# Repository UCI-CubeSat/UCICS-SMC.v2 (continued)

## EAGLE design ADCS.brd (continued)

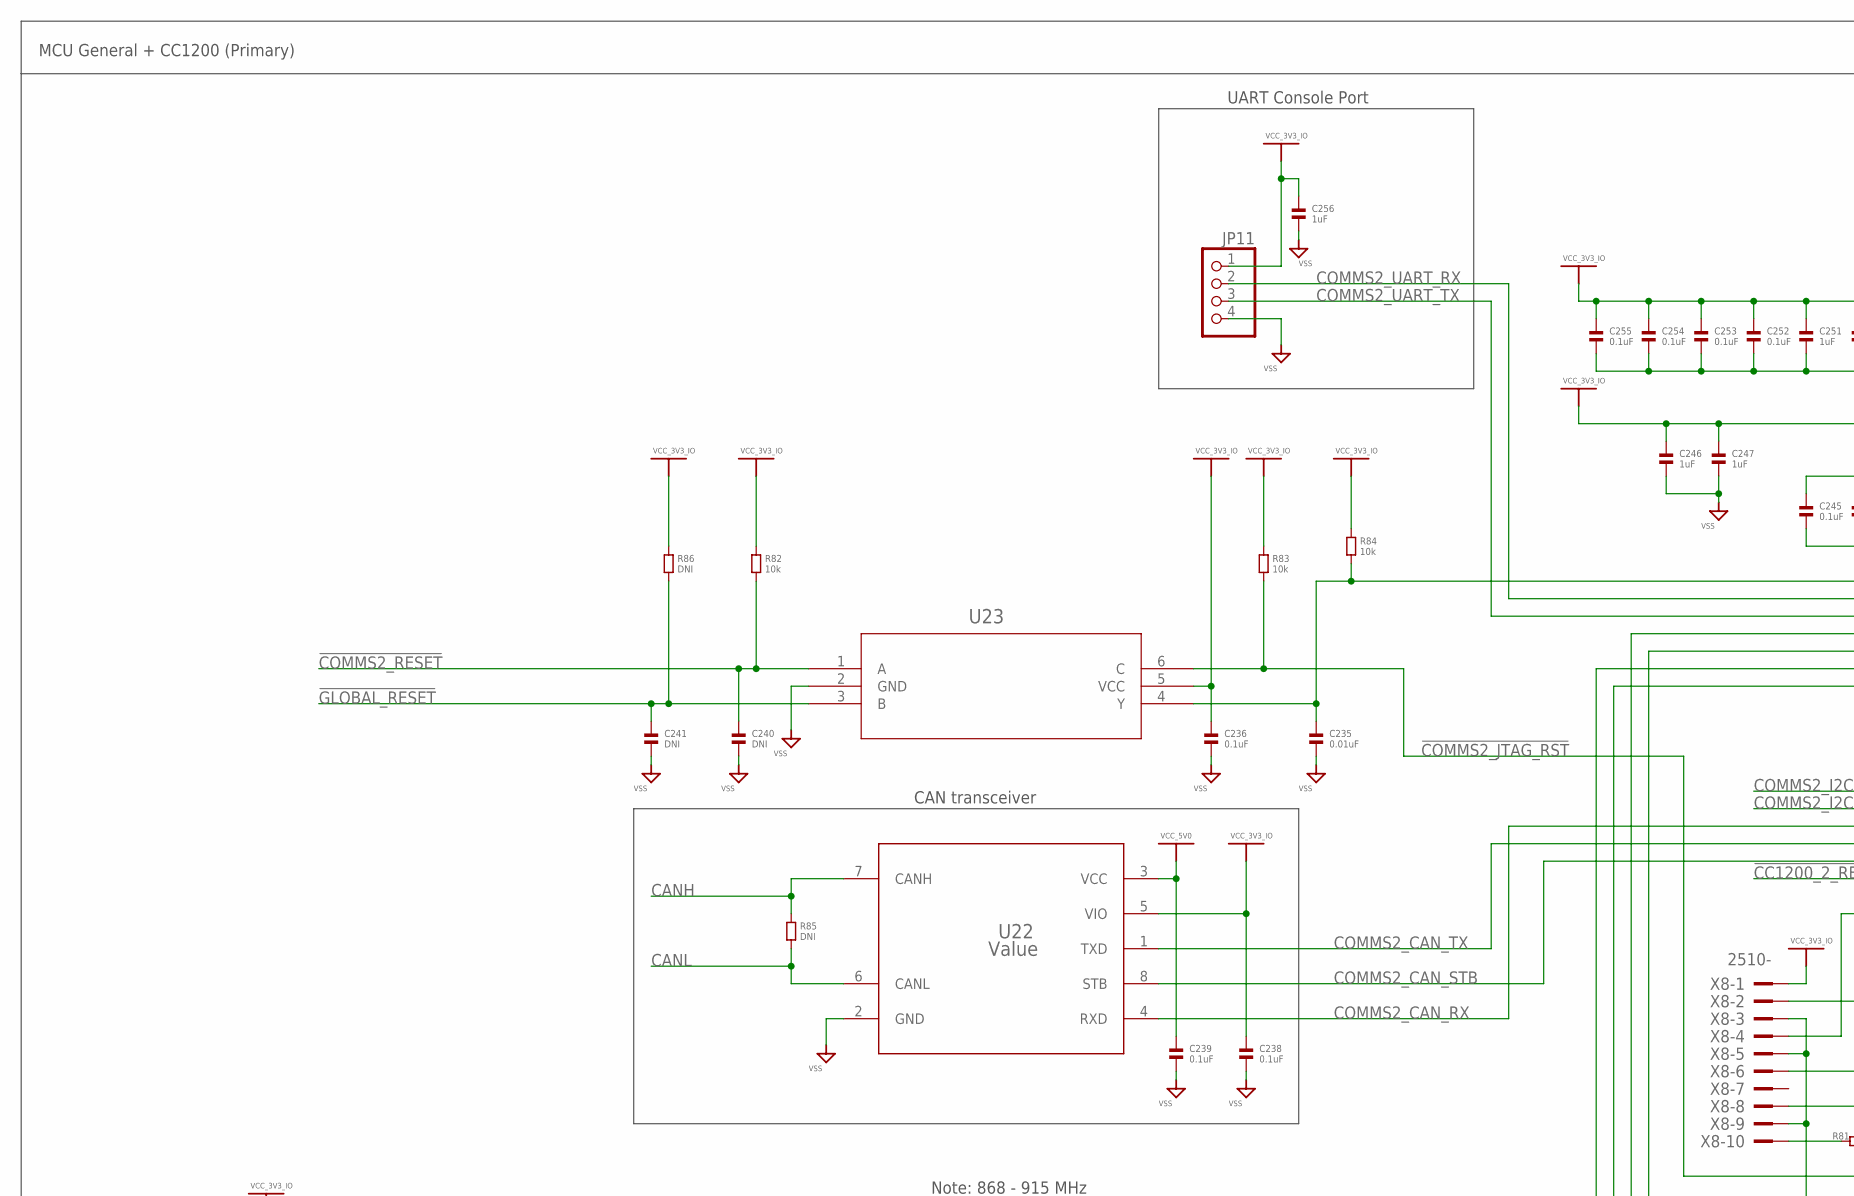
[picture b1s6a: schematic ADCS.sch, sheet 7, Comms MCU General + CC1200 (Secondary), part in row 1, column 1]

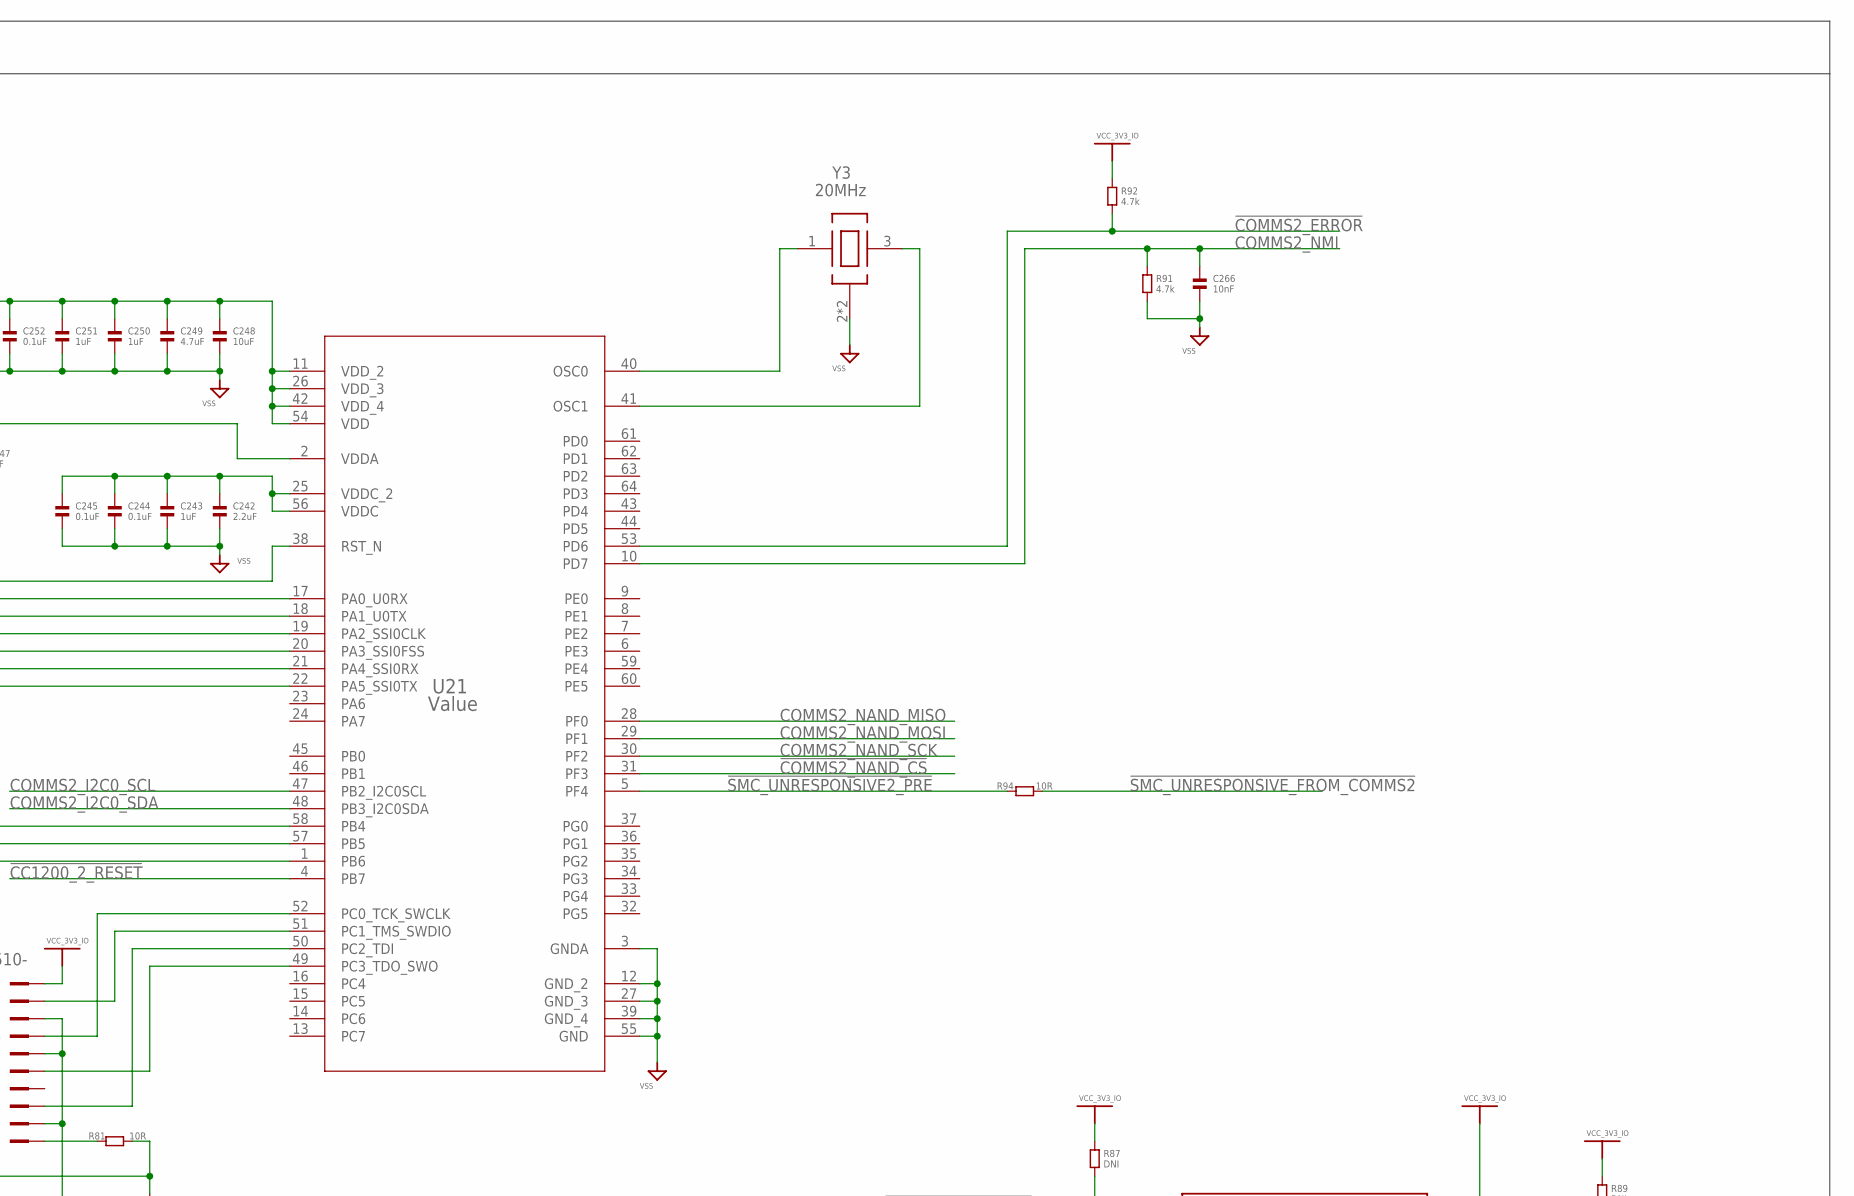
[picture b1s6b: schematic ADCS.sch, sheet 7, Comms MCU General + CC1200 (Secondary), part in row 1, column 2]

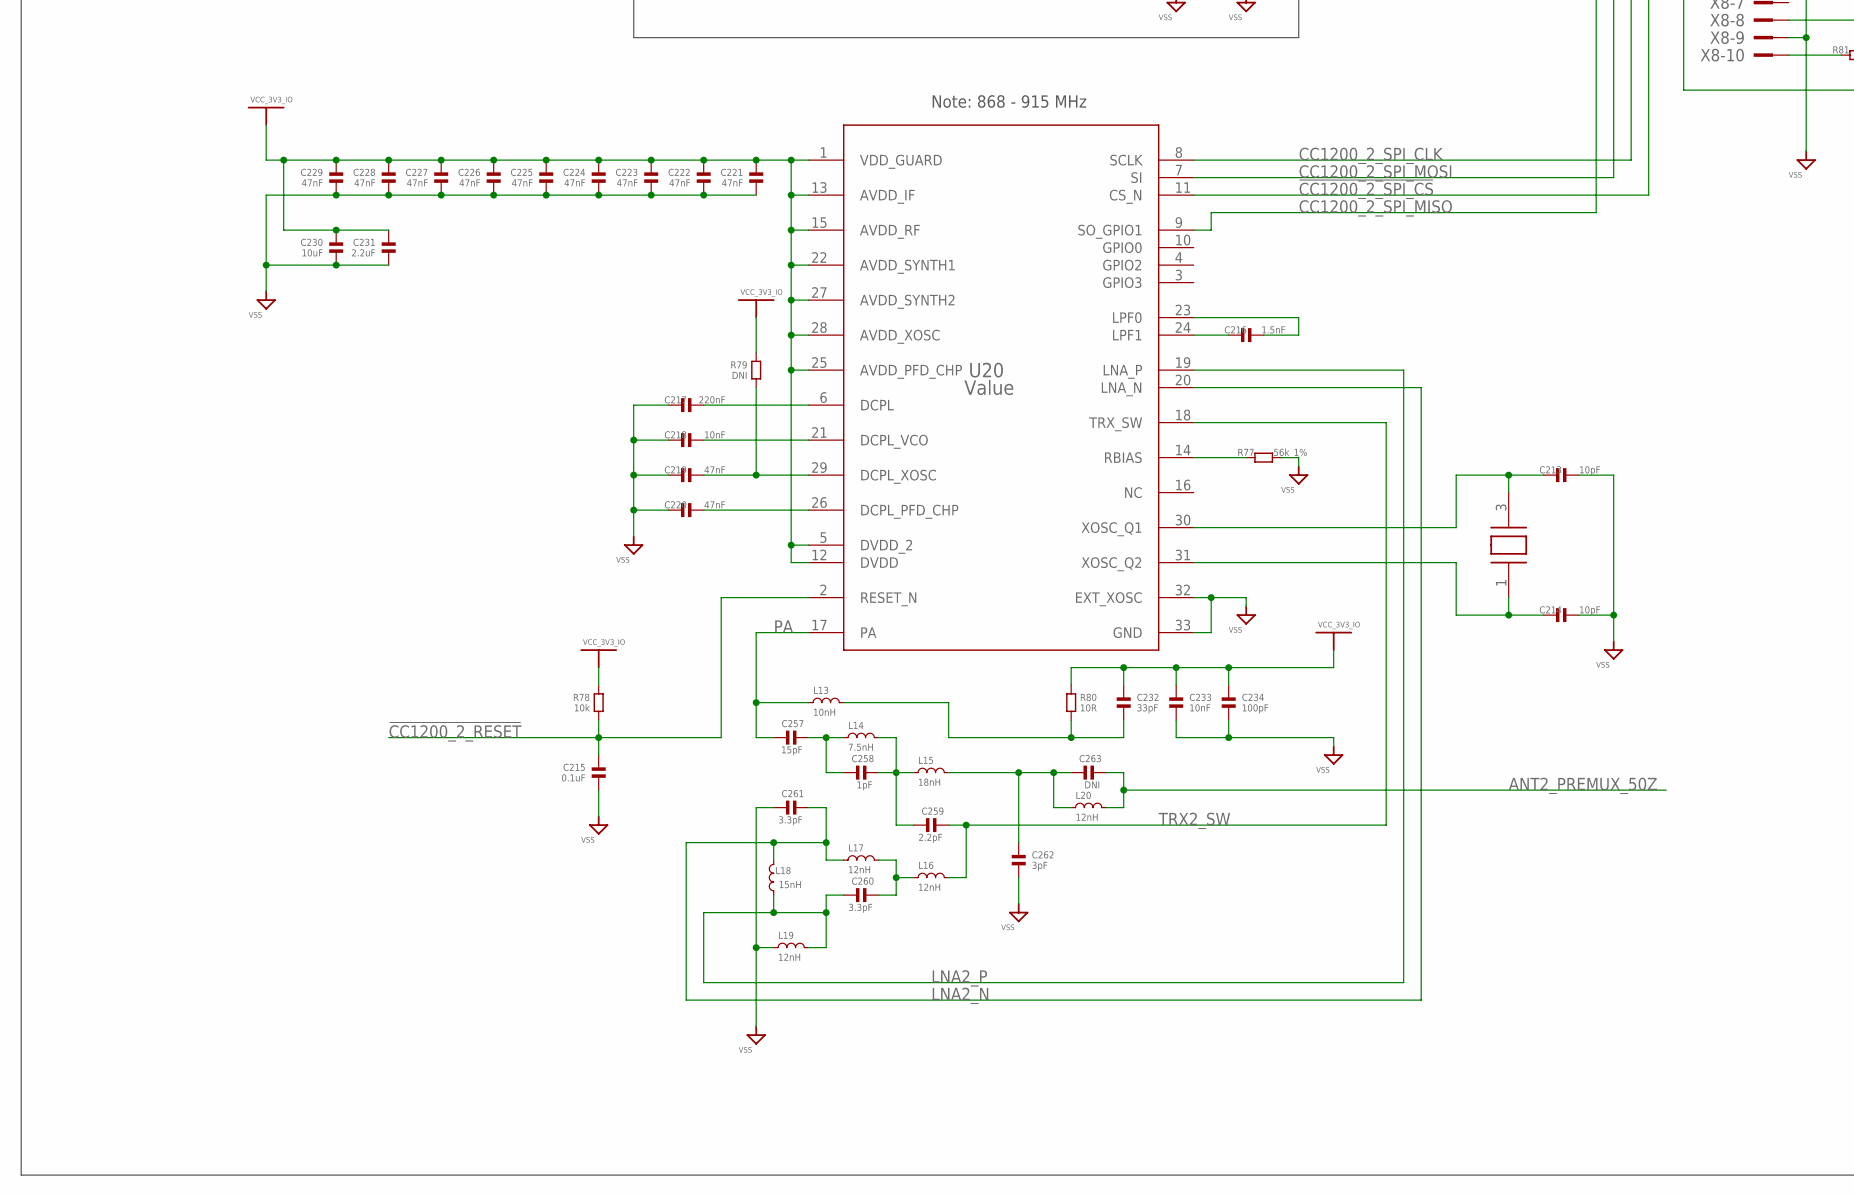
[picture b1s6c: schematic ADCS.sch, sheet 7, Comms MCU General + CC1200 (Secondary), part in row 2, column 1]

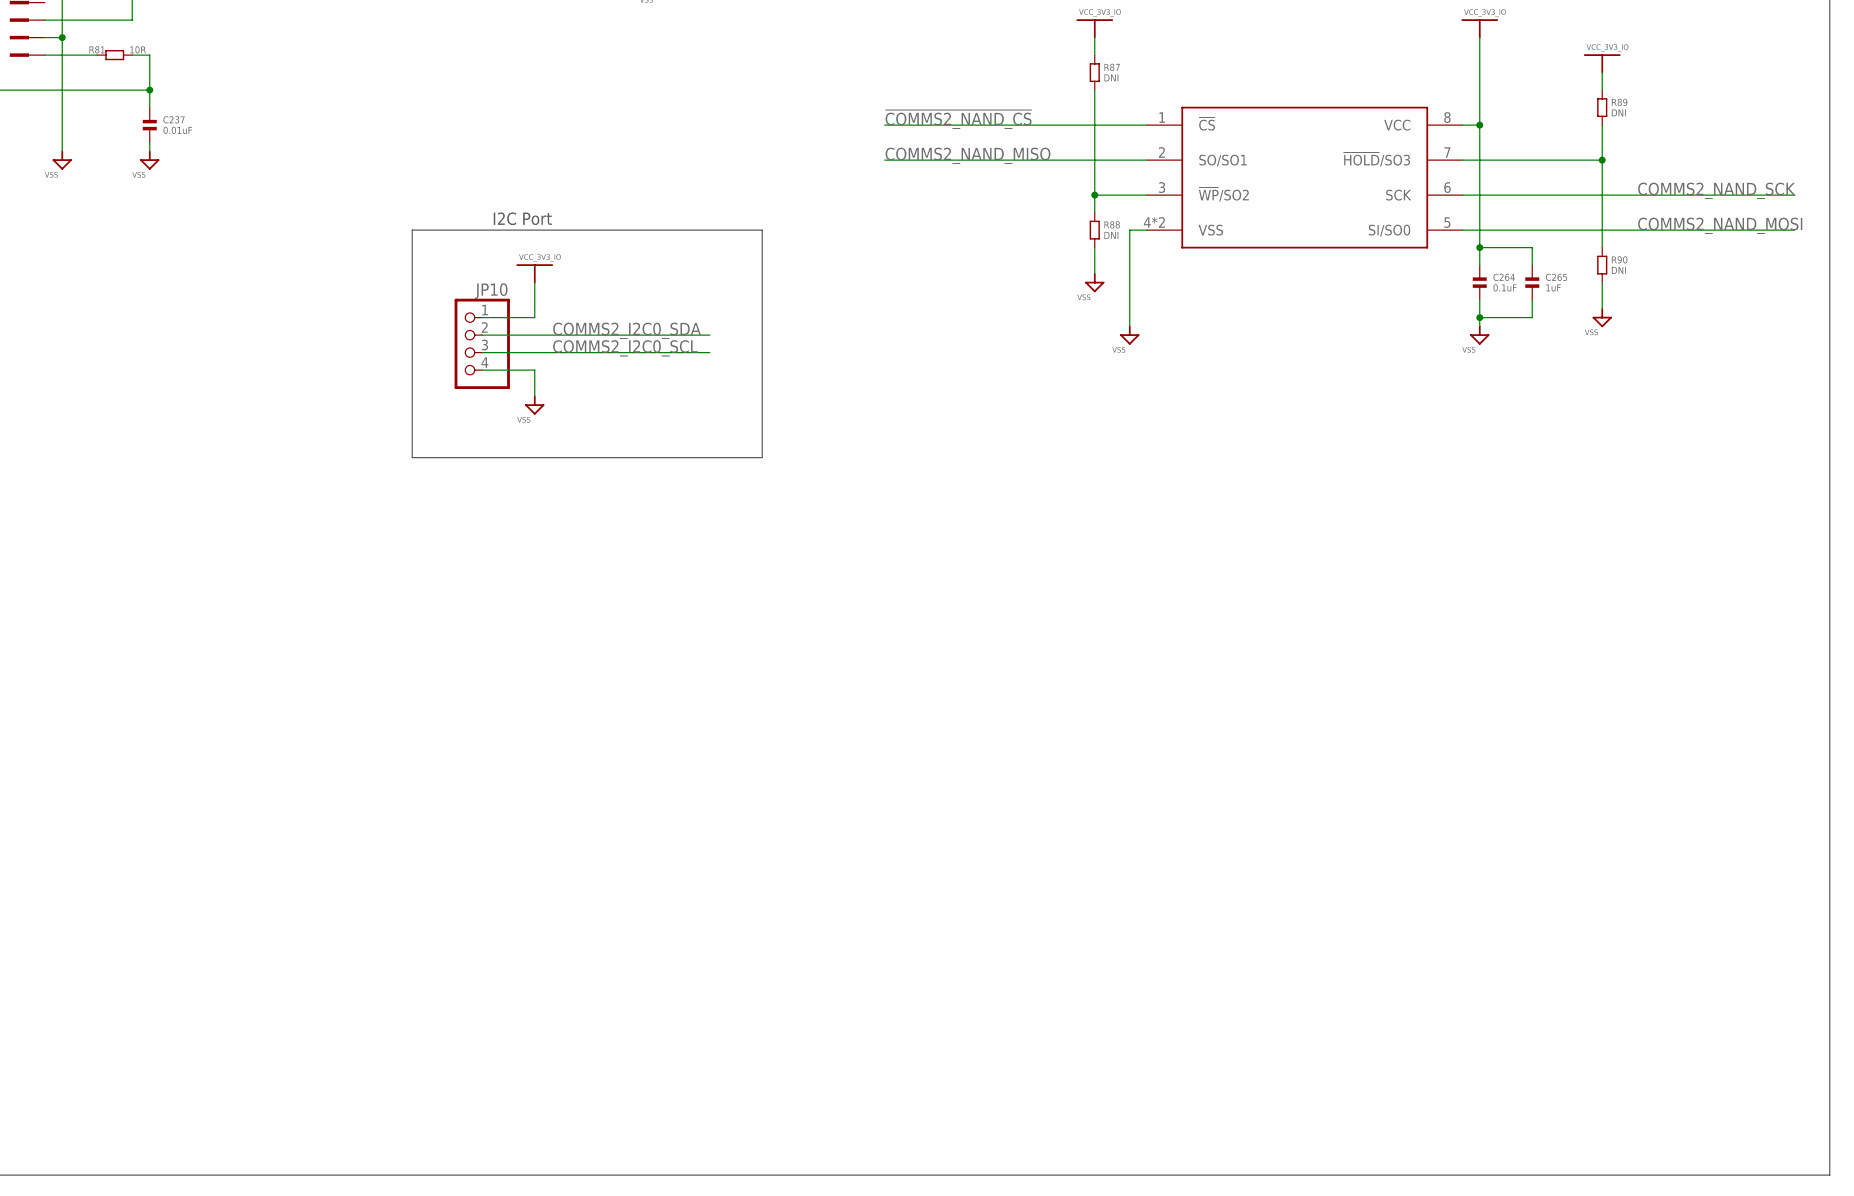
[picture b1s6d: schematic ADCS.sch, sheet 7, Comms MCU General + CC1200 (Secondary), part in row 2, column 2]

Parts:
C213, C214: 10pF; 0603
C215, C236, C238, C239, C244, C245, C252, C253, C254, C255, C264: 0.1uF; 0603
C216: 1.5nF; 0402
C217: 220nF; 0402
C218, C233: 10nF; 0402
C219, C220, C221, C222, C223, C224, C225, C226, C227, C228, C229: 47nF; 0402
C230, C248: 10uF; 0603
C231, C242: 2.2uF; 0603
C232: 33pF; 0402
C234: 100pF; 0402
C235, C237: 0.01uF; 0603
C240, C241: DNI; 0603
C243, C246, C247, C250, C251, C256, C265: 1uF; 0603
C249: 4.7uF; 0603
C257: 15pF; 0402
C258: 1pF; 0402
C259: 2.2pF; 0402
C260, C261: 3.3pF; 0402
C262: 3pF; 0402
C263: DNI; 0402
C266: 10nF; 0603
JP10, JP11: PINHD-1X4; 1X04
L13: 10nH; 0402
L14: 7.5nH; 0402
L15: 18nH; 0402
L16, L17, L19, L20: 12nH; 0402
L18: 15nH; 0402
R77: 56k_1%; 0603
R78, R82, R83, R84: 10k; 0603
R79: DNI; 0402
R80: 10R; 0402
R81, R94: 10R; 0603
R85, R86, R87, R88, R89, R90: DNI; 0603
R91, R92: 4.7k; 0603
U20: Value; TEXAS_INSTRUMENTS-RADAR-CC1200RHBR
U21: Value; PM0064A_N
U22: Value; TEXAS_INSTRUMENTS-CAN_TRANSCEIVER-TCAN1042/LED_DRIVER-TLC59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
U23: TEXAS_INSTRUMENTS-AND_GATE-SN74LVC1G11_DCK_6
U24: KIOXIA_AMERICA-NAND_FLASH-TC58CVG0S3HRAIG
X7: ECS_INC-OSCILLATOR-ECS-400-10-37-CKM-TR
X8: 2510-; PAK100/2500-10
Y3: 20MHz; ESC-OSCILLATOR-ECS_200_9_33B_CTP_TR

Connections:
!CC1200_2_RESET: C215.1, R78.2, U20.2 (RESET_N), U21.4 (PB7)
!CC1200_2_SPI_CS: U20.11 (CS_N), U21.20 (PA3_SSI0FSS)
!COMMS2_ERROR: R92.2, U21.53 (PD6); also elsewhere on the board
!COMMS2_JTAG_RST: C237.1, R81.2, R83.2, U23.6 (C)
!COMMS2_NAND_CS: U21.31 (PF3), U24.1 (!CS)
!COMMS2_RESET: C240.1, R82.2, U23.1 (A); also elsewhere on the board
!GLOBAL_RESET: C241.1, R86.2, U23.3 (B); also elsewhere on the board
!SMC_UNRESPONSIVE2_PRE: R94.1, U21.5 (PF4)
!SMC_UNRESPONSIVE_FROM_COMMS2: R94.2; also elsewhere on the board
ANT2_PREMUX_50Z: C263.2, L20.2; also elsewhere on the board
CANH: R85.1, U22.7 (CANH); also elsewhere on the board
CANL: R85.2, U22.6 (CANL); also elsewhere on the board
CC1200_2_SPI_CLK: U20.8 (SCLK), U21.19 (PA2_SSI0CLK)
CC1200_2_SPI_MISO: U20.9 (SO_GPIO1), U21.21 (PA4_SSI0RX)
CC1200_2_SPI_MOSI: U20.7 (SI), U21.22 (PA5_SSI0TX)
COMMS2_CAN_RX: U21.58 (PB4), U22.4 (RXD)
COMMS2_CAN_STB: U21.1 (PB6), U22.8 (STB)
COMMS2_CAN_TX: U21.57 (PB5), U22.1 (TXD)
COMMS2_I2C0_SCL: JP10.3, U21.47 (PB2_I2C0SCL)
COMMS2_I2C0_SDA: JP10.2, U21.48 (PB3_I2C0SDA)
COMMS2_NAND_MISO: U21.28 (PF0), U24.2 (SO/SO1)
COMMS2_NAND_MOSI: U21.29 (PF1), U24.5 (SI/SO0)
COMMS2_NAND_SCK: U21.30 (PF2), U24.6 (SCK)
COMMS2_NMI: C266.1, R91.1, U21.10 (PD7); also elsewhere on the board
COMMS2_UART_RX: JP11.2, U21.17 (PA0_U0RX); also elsewhere on the board
COMMS2_UART_TX: JP11.3, U21.18 (PA1_U0TX); also elsewhere on the board
LNA2_N: C261.2, L17.1, L18.2, U20.20 (LNA_N)
LNA2_P: C260.1, L18.1, L19.2, U20.19 (LNA_P)
unnamed: R77.1, U20.14 (RBIAS)
unnamed: C213.1, U20.30 (XOSC_Q1), X7.3 (XO)
unnamed: C214.1, U20.31 (XOSC_Q2), X7.1 (XI)
unnamed: C216.1, U20.24 (LPF1)
unnamed: C216.2, U20.23 (LPF0)
unnamed: C220.2, U20.26 (DCPL_PFD_CHP)
unnamed: C219.2, R79.2, U20.29 (DCPL_XOSC)
unnamed: C218.2, U20.21 (DCPL_VCO)
unnamed: C217.2, U20.6 (DCPL)
unnamed: C232.2, L13.2, R80.2
unnamed: R81.1, X8.10
unnamed: C235.1, R84.2, U21.38 (RST_N), U23.4 (Y)
unnamed: U21.50 (PC2_TDI), X8.8
unnamed: U21.49 (PC3_TDO_SWO), X8.6
unnamed: U21.51 (PC1_TMS_SWDIO), X8.2
unnamed: U21.52 (PC0_TCK_SWCLK), X8.4
unnamed: C242.1, C243.1, C244.1, C245.1, U21.25 (VDDC_2), U21.56 (VDDC)
unnamed: U21.40 (OSC0), Y3.1 (XI)
unnamed: U21.41 (OSC1), Y3.3 (XO)
unnamed: C257.2, C258.1, L14.1
unnamed: C258.2, C259.1, L14.2, L15.1
unnamed: C260.2, L16.1, L17.2
unnamed: C262.1, C263.1, L15.2, L20.1
unnamed: R87.2, R88.1, U24.3 (!WP!/SO2)
unnamed: R89.2, R90.1, U24.7 (!HOLD!/SO3)
PA: C257.1, L13.1, U20.17 (PA); also elsewhere on the board
TRX2_SW: C259.2, L16.2, U20.18 (TRX_SW)
VCC_3V3_IO: C221.1, C222.1, C223.1, C224.1, C225.1, C226.1, C227.1, C228.1, C229.1, C230.1, C231.1, C232.1, C233.1, C234.1, C236.1, C238.1, C246.1, C247.1, C248.1, C249.1, C250.1, C251.1, C252.1, C253.1, C254.1, C255.1, C256.1, C264.1, C265.1, JP10.1, JP11.1, R78.1, R79.1, R80.1, R82.1, R83.1, R84.1, R86.1, R87.1, R89.1, R92.1, U20.1 (VDD_GUARD), U20.5 (DVDD_2), U20.12 (DVDD), U20.13 (AVDD_IF), U20.15 (AVDD_RF), U20.22 (AVDD_SYNTH1), U20.25 (AVDD_PFD_CHP), U20.27 (AVDD_SYNTH2), U20.28 (AVDD_XOSC), U21.2 (VDDA), U21.11 (VDD_2), U21.26 (VDD_3), U21.42 (VDD_4), U21.54 (VDD), U22.5 (VIO), U23.5 (VCC), U24.8 (VCC), X8.1; also elsewhere on the board
VCC_5V0: C239.1, U22.3 (VCC); also elsewhere on the board
VSS: C213.2, C214.2, C215.2, C217.1, C218.1, C219.1, C220.1, C221.2, C222.2, C223.2, C224.2, C225.2, C226.2, C227.2, C228.2, C229.2, C230.2, C231.2, C233.2, C234.2, C235.2, C236.2, C237.2, C238.2, C239.2, C240.2, C241.2, C242.2, C243.2, C244.2, C245.2, C246.2, C247.2, C248.2, C249.2, C250.2, C251.2, C252.2, C253.2, C254.2, C255.2, C256.2, C261.1, C262.2, C264.2, C265.2, C266.2, JP10.4, JP11.4, L19.1, R77.2, R88.2, R90.2, R91.2, U20.32 (EXT_XOSC), U20.33 (GND), U21.3 (GNDA), U21.12 (GND_2), U21.27 (GND_3), U21.39 (GND_4), U21.55 (GND), U22.2 (GND), U23.2 (GND), U24.4 (VSS), U24.9 (VSS), X8.3, X8.5, X8.9, Y3.2 (VSS), Y3.4 (VSS); also elsewhere on the board

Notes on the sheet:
Note: 868 - 915 MHz
MCU General + CC1200 (Primary)
CAN transceiver
I2C Port
UART Console Port

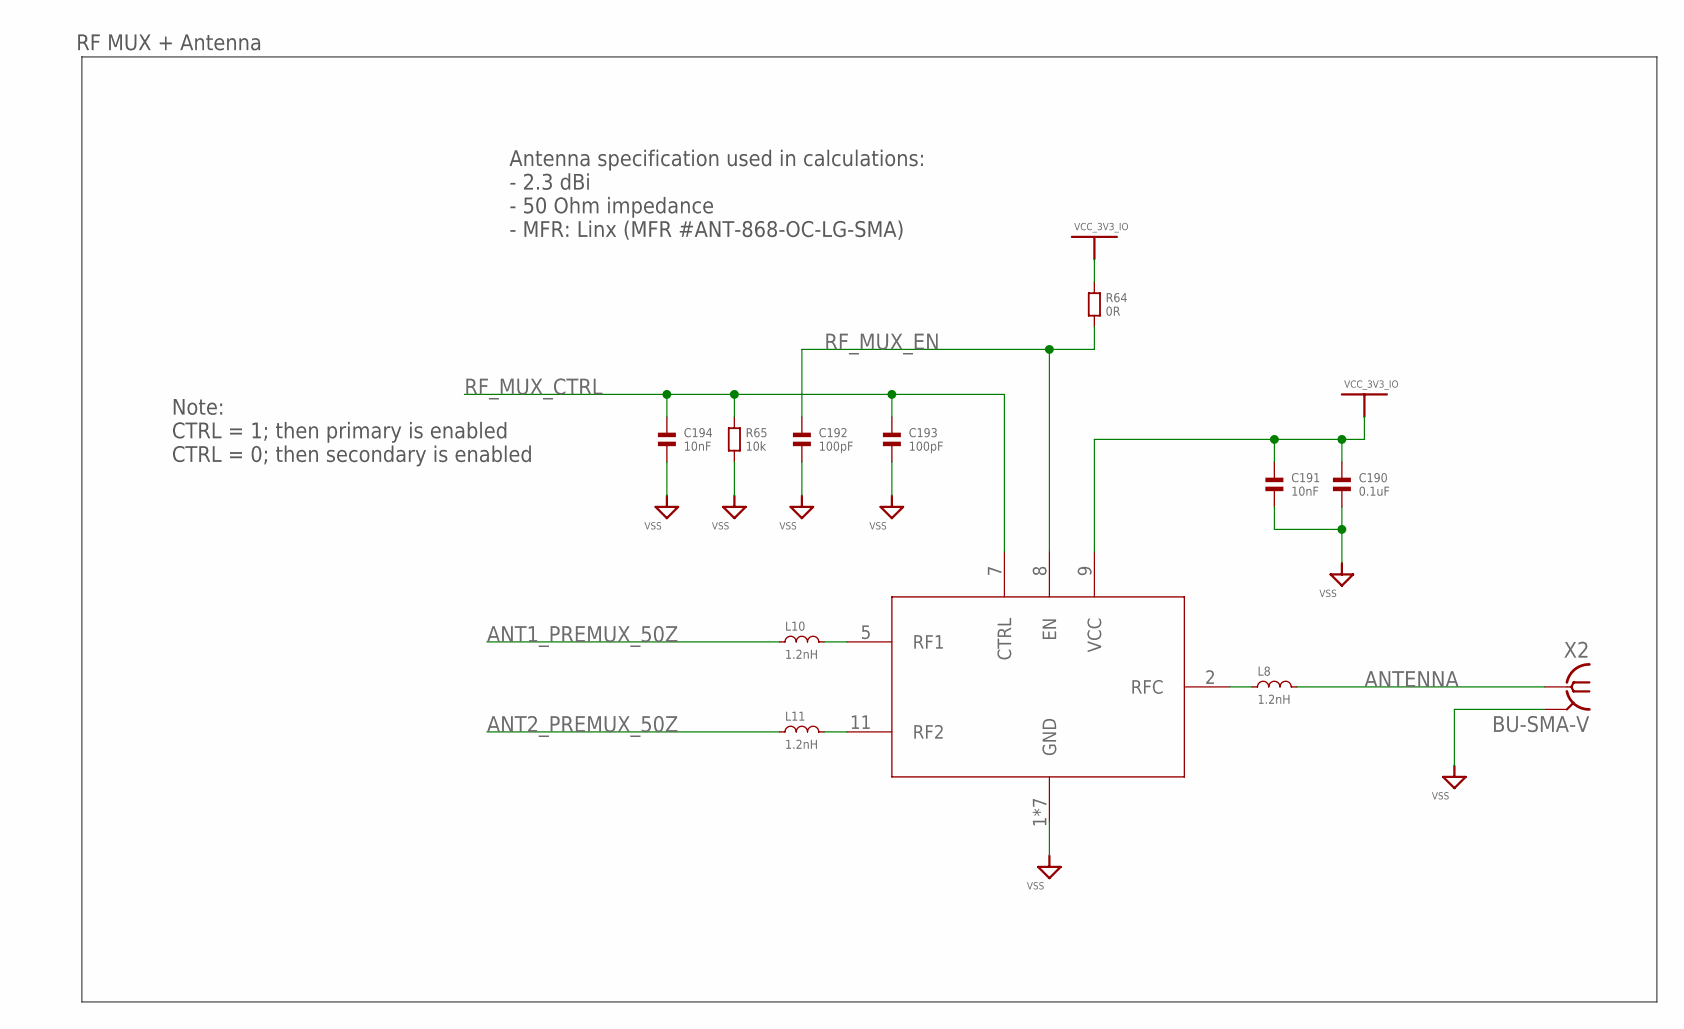
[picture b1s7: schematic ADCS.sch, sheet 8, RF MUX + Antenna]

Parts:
C190: 0.1uF; 0603
C191, C194: 10nF; 0603
C192, C193: 100pF; 0603
L8, L10, L11: 1.2nH; 0402
R64: 0R; 0603
R65: 10k; 0603
U17: QORVO-RF_SWITCH-QPC7512
X2: BU-SMA-V

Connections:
ANT1_PREMUX_50Z: L10.1; also elsewhere on the board
ANT2_PREMUX_50Z: L11.1; also elsewhere on the board
ANTENNA: L8.2, X2.1
unnamed: L8.1, U17.2 (RFC)
unnamed: L11.2, U17.11 (RF2)
unnamed: L10.2, U17.5 (RF1)
RF_MUX_CTRL: C193.1, C194.1, R65.1, U17.7 (CTRL); also elsewhere on the board
RF_MUX_EN: C192.1, R64.2, U17.8 (EN)
VCC_3V3_IO: C190.1, C191.1, R64.1, U17.9 (VCC); also elsewhere on the board
VSS: C190.2, C191.2, C192.2, C193.2, C194.2, R65.2, U17.1 (GND), U17.3 (GND), U17.4 (GND), U17.6 (GND), U17.10 (GND), U17.12 (GND), U17.13 (GND), X2.2, X2.3 (2), X2.4 (2), X2.5 (2); also elsewhere on the board

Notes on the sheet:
Antenna specification used in calculations: - 2.3 dBi - 50 Ohm impedance - MFR: Linx (MFR #ANT-868-OC-LG-SMA)
Note: CTRL = 1; then primary is enabled CTRL = 0; then secondary is enabled
RF MUX + Antenna

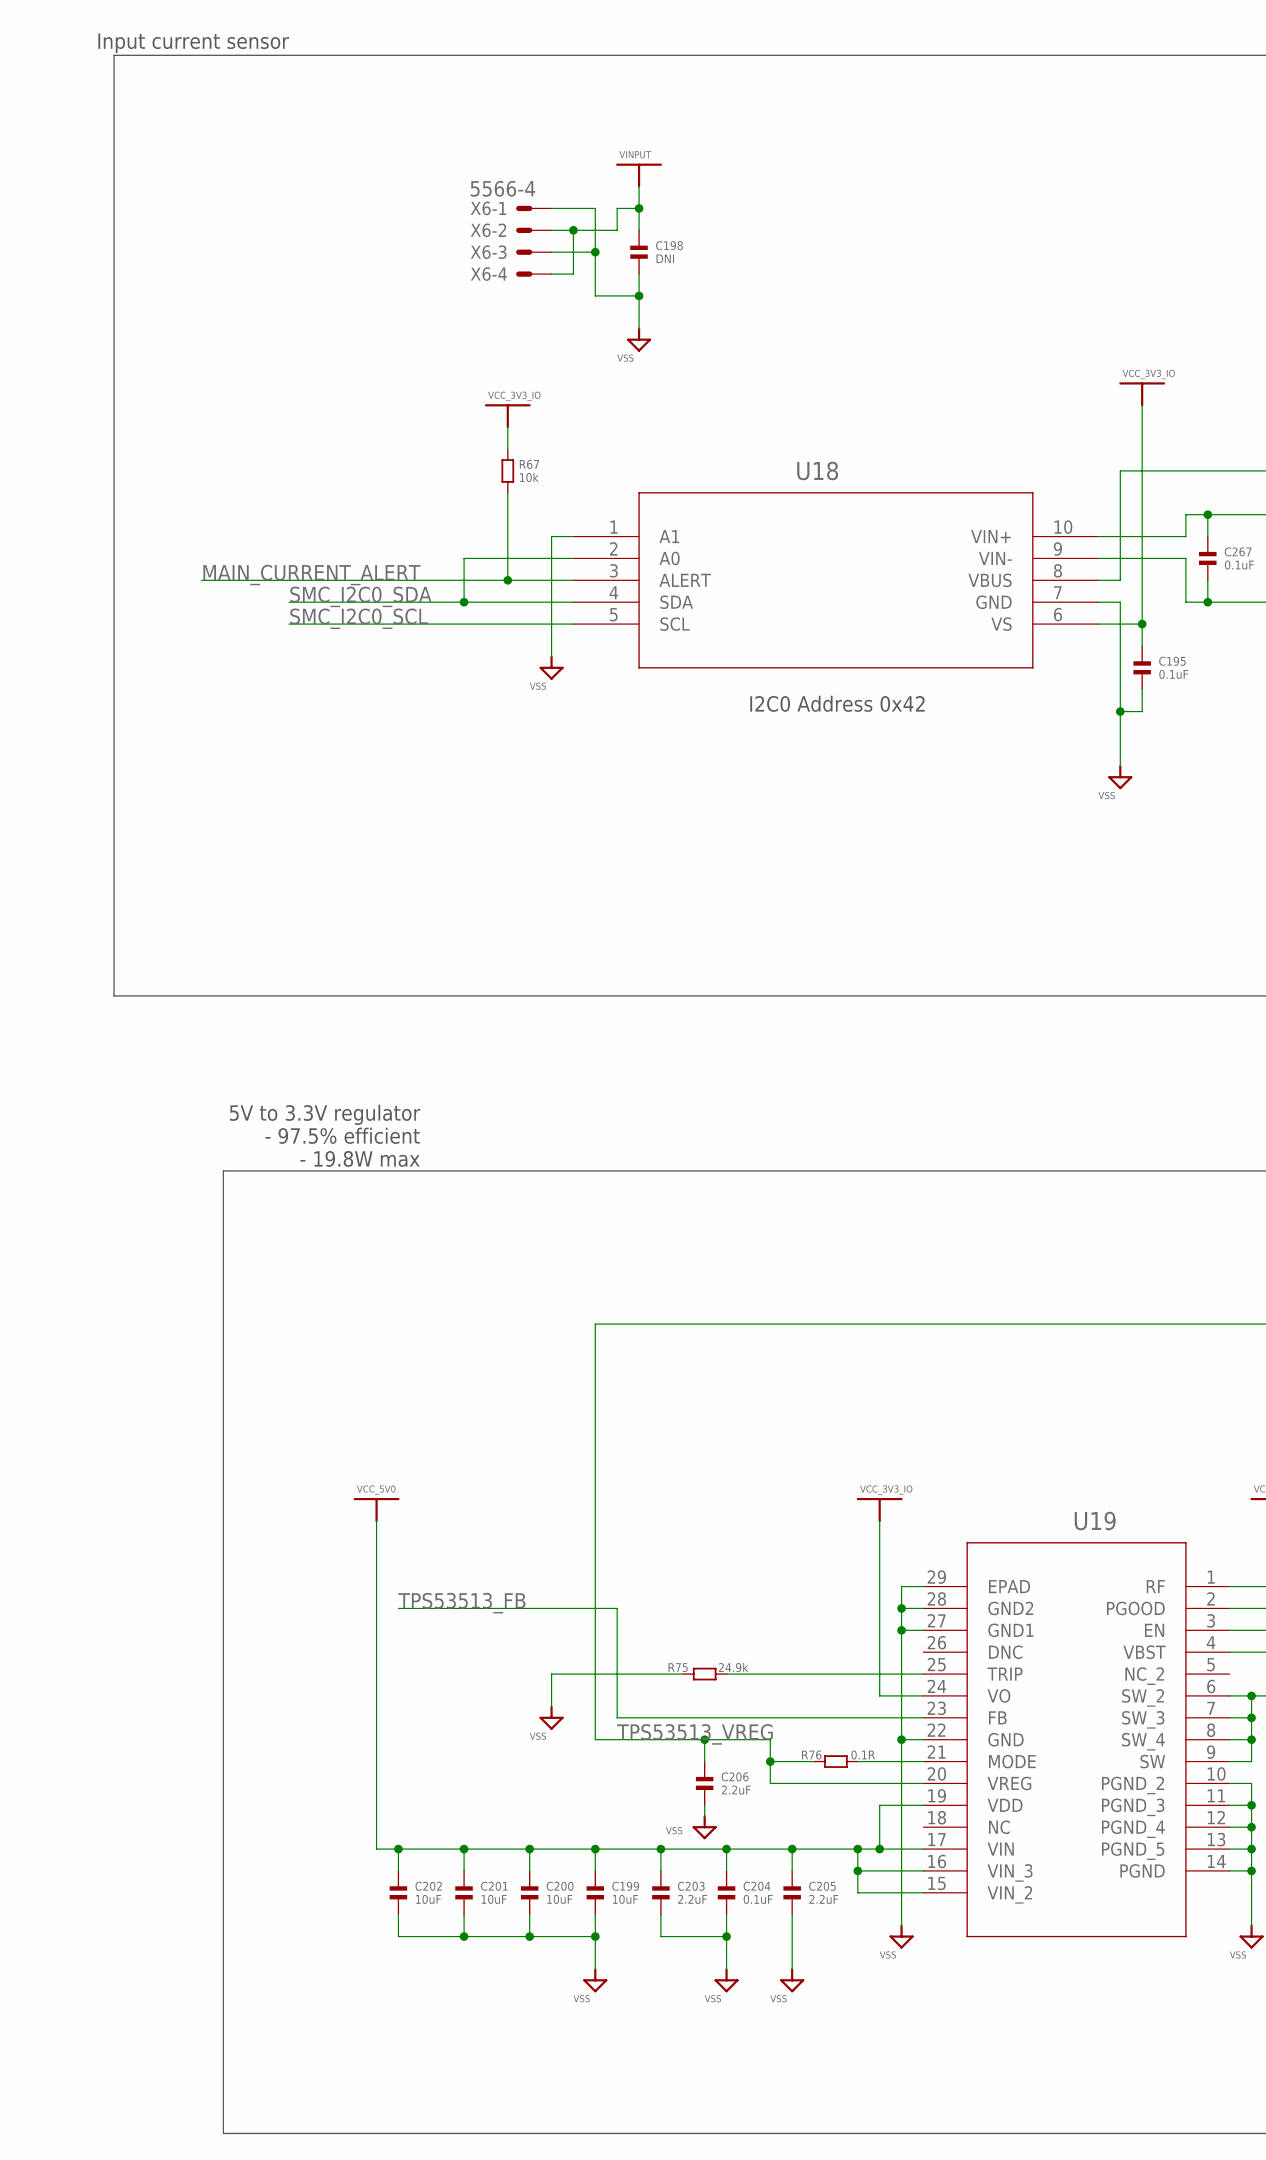
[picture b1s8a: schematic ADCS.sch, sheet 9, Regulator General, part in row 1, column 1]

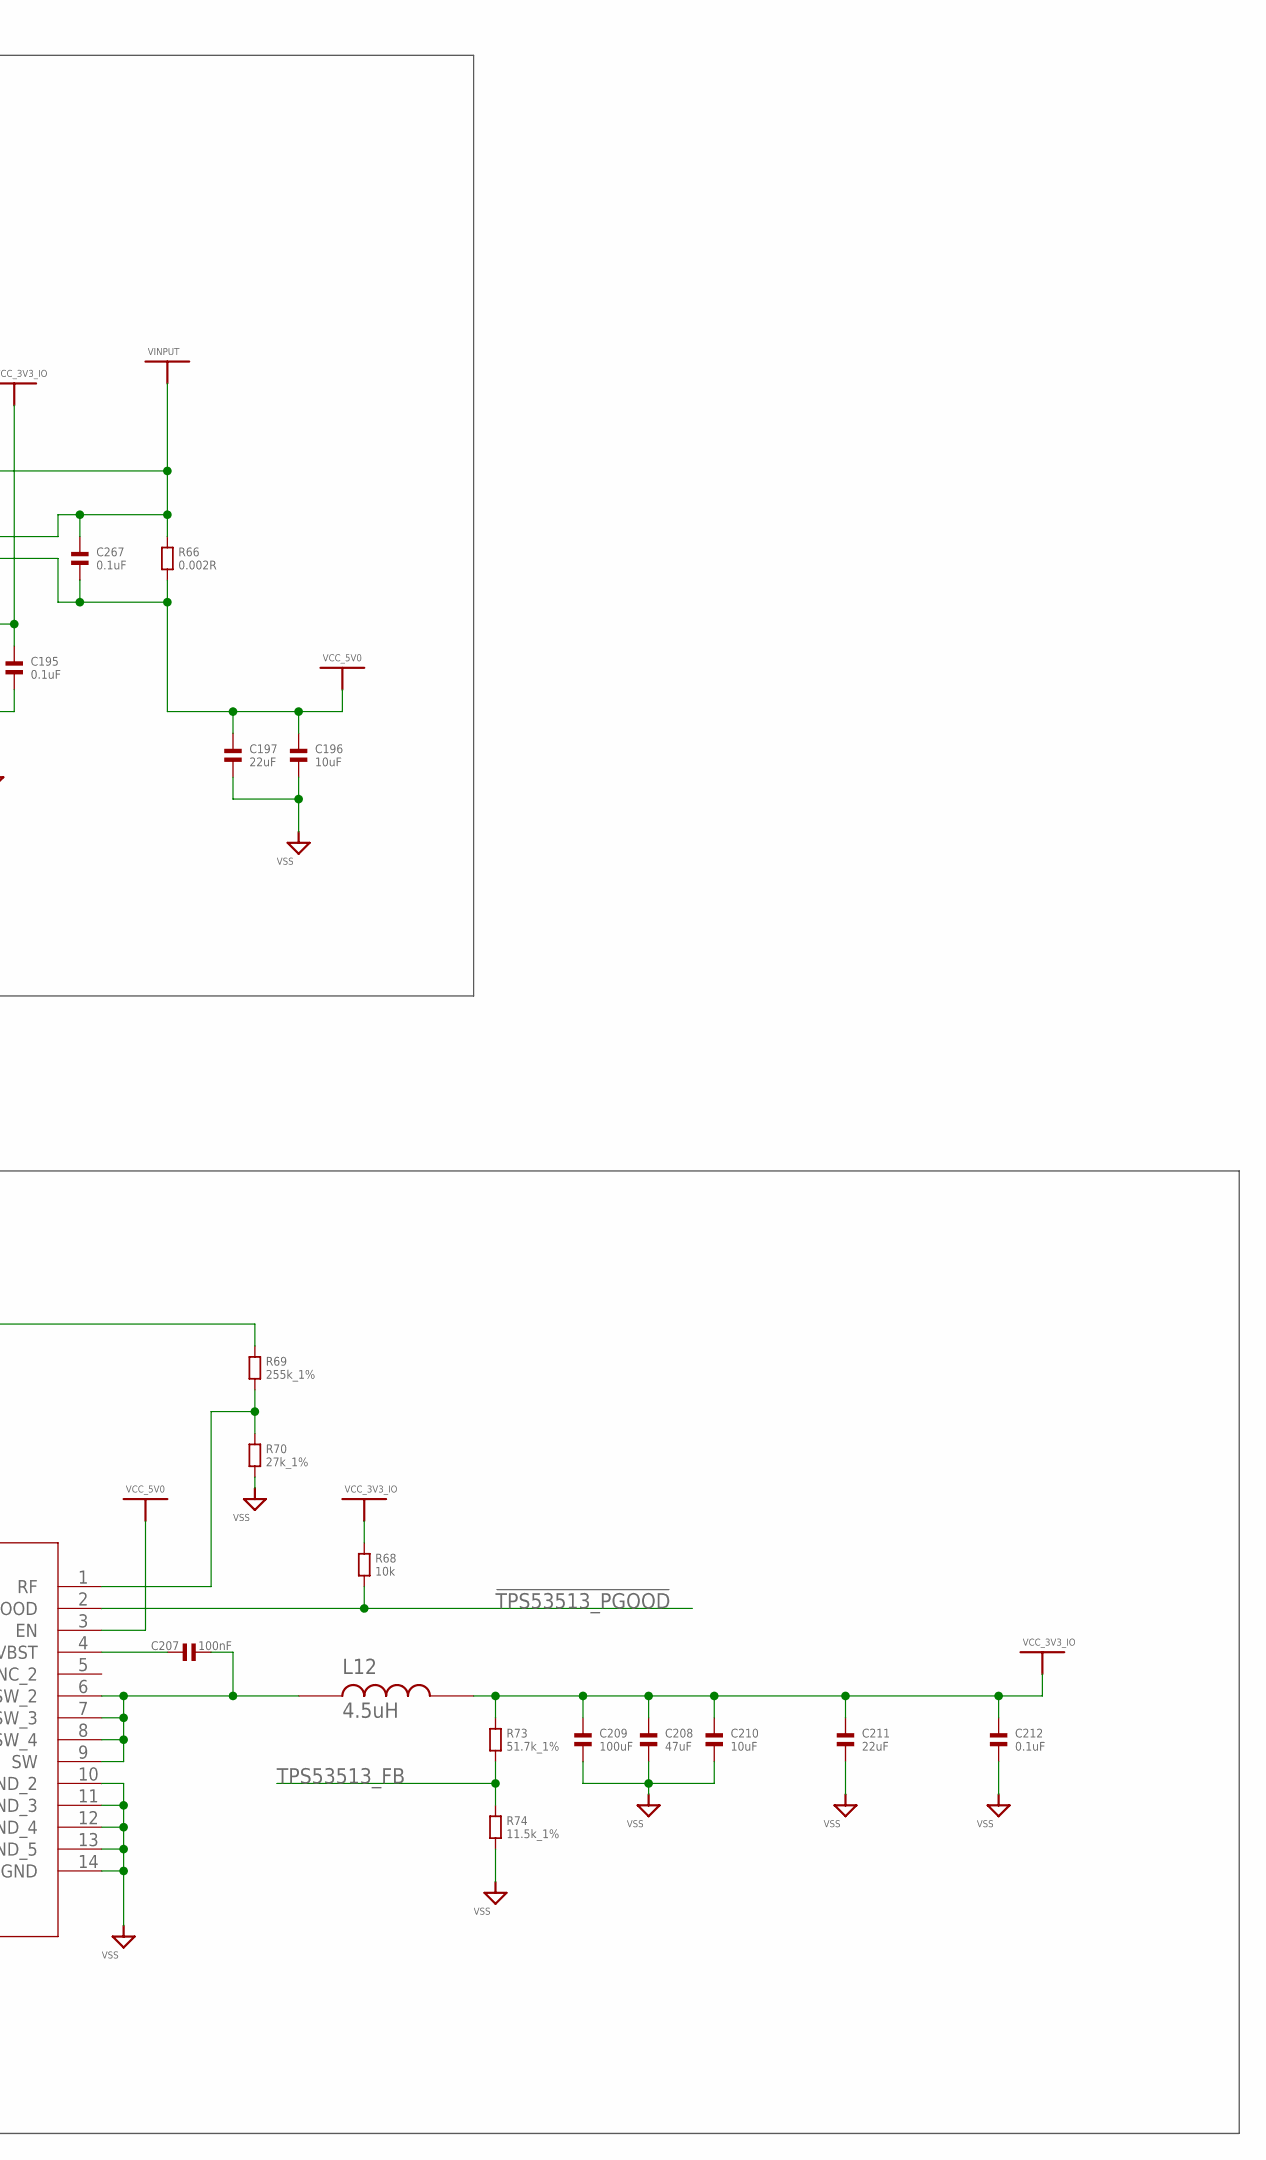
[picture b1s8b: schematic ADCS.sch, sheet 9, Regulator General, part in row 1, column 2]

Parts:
C195, C204, C267: 0.1uF; 0603
C196, C199, C200, C201, C202, C210: 10uF; 0805
C197, C211: 22uF; 0805
C198: DNI; 0805
C203, C205, C206: 2.2uF; 0603
C207: 100nF; 0805
C208: 47uF; 1206
C209: 100uF; 1206
C212: 0.1uF; 0805
L12: 4.5uH; BOURNS-INDUCTOR-SRR1208-4R5ML
R66: 0.002R; 1812
R67, R68: 10k; 0603
R69: 255k_1%; 0603
R70: 27k_1%; 0603
R73: 51.7k_1%; 0603
R74: 11.5k_1%; 0603
R75: 24.9k; 0603
R76: 0.1R; 0603
U18: TEXAS_INSTRUMENTS-CURRENT_MONITOR-INA226_DGS_10
U19: TEXAS_INSTRUMENTS-BUCK_CONVERTER-TPS53513RVER; RVE28_TEX
X6: 5566-4

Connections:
!TPS53513_PGOOD: R68.2, U19.2 (PGOOD); also elsewhere on the board
MAIN_CURRENT_ALERT: R67.2, U18.3 (ALERT); also elsewhere on the board
unnamed: R69.2, R70.1, U19.1 (RF)
unnamed: C207.1, U19.4 (VBST)
unnamed: C207.2, L12.1, U19.6 (SW_2), U19.7 (SW_3), U19.8 (SW_4), U19.9 (SW)
unnamed: R75.2, U19.25 (TRIP)
unnamed: R76.2, U19.21 (MODE)
SMC_I2C0_SCL: U18.5 (SCL); also elsewhere on the board
SMC_I2C0_SDA: U18.2 (A0), U18.4 (SDA); also elsewhere on the board
TPS53513_FB: R73.2, R74.1, U19.23 (FB)
TPS53513_VREG: C206.1, R69.1, R76.1, U19.20 (VREG)
VCC_3V3_IO: C195.1, C208.1, C209.1, C210.1, C211.1, C212.1, L12.2, R67.1, R68.1, R73.1, U18.6 (VS), U19.24 (VO); also elsewhere on the board
VCC_5V0: C196.1, C197.1, C199.1, C200.1, C201.1, C202.1, C203.1, C204.1, C205.1, C267.2, R66.2, U18.9 (VIN-), U19.3 (EN), U19.15 (VIN_2), U19.16 (VIN_3), U19.17 (VIN), U19.19 (VDD); also elsewhere on the board
VINPUT: C198.1, C267.1, R66.1, U18.8 (VBUS), U18.10 (VIN+), X6.2, X6.4
VSS: C195.2, C196.2, C197.2, C198.2, C199.2, C200.2, C201.2, C202.2, C203.2, C204.2, C205.2, C206.2, C208.2, C209.2, C210.2, C211.2, C212.2, R70.2, R74.2, R75.1, U18.1 (A1), U18.7 (GND), U19.10 (PGND_2), U19.11 (PGND_3), U19.12 (PGND_4), U19.13 (PGND_5), U19.14 (PGND), U19.22 (GND), U19.27 (GND1), U19.28 (GND2), U19.29 (EPAD), X6.1, X6.3; also elsewhere on the board

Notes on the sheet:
I2C0 Address 0x42
5V to 3.3V regulator - 97.5% efficient - 19.8W max
Input current sensor

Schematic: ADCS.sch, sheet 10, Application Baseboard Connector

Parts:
C167, C169: 2.2uF; 0603
C168, C170: 0.1uF; 0603
J1: SEAF-10-XX.X-XX-04-X-A

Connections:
ADCS_ERROR: J1.C10 (10); also elsewhere on the board
ADCS_FAILURE: J1.A10 (10)
ADCS_ONLINE: J1.C9 (9); also elsewhere on the board
CANH: J1.A7 (7); also elsewhere on the board
CANL: J1.A8 (8); also elsewhere on the board
COMMS1_UART_RX: J1.C5 (5); also elsewhere on the board
COMMS1_UART_TX: J1.C4 (4); also elsewhere on the board
COMMS2_UART_RX: J1.C8 (8); also elsewhere on the board
COMMS2_UART_TX: J1.C7 (7); also elsewhere on the board
CPLD_I1: J1.D3 (3); also elsewhere on the board
CPLD_I2: J1.D4 (4); also elsewhere on the board
CPLD_I3: J1.D5 (5); also elsewhere on the board
CPLD_I4: J1.D6 (6); also elsewhere on the board
CPLD_O1: J1.D7 (7); also elsewhere on the board
CPLD_O2: J1.D8 (8); also elsewhere on the board
CPLD_O3: J1.D9 (9); also elsewhere on the board
CPLD_O4: J1.D10 (10); also elsewhere on the board
SMC_I2C0_SCL: J1.A2 (2); also elsewhere on the board
SMC_I2C0_SDA: J1.A1 (1); also elsewhere on the board
SMC_I2C1_SCL: J1.A5 (5); also elsewhere on the board
SMC_I2C1_SDA: J1.A4 (4); also elsewhere on the board
SMC_UART0_RX: J1.C2 (2); also elsewhere on the board
SMC_UART0_TX: J1.C1 (1); also elsewhere on the board
VCC_3V3_IO: C167.1, C170.1, J1.B3 (3), J1.B4 (4); also elsewhere on the board
VCC_5V0: C168.1, C169.1, J1.B1 (1), J1.B2 (2); also elsewhere on the board
VSS: C167.2, C168.2, C169.2, C170.2, J1.A3 (3), J1.A6 (6), J1.A9 (9), J1.B5 (5), J1.B6 (6), J1.B7 (7), J1.B8 (8), J1.B9 (9), J1.B10 (10), J1.C3 (3), J1.C6 (6), J1.D1 (1), J1.D2 (2); also elsewhere on the board
